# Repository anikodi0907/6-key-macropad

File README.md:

# 6-key-macropad
A simple macropad with 6 switches. VIA compatible, uses arduino pro micro.

Follow the [build guide](https://github.com/anikodi0907/6-key-macropad/blob/main/Build%20guide.md) to build the pcb.

## Photos
Fully built

Design images

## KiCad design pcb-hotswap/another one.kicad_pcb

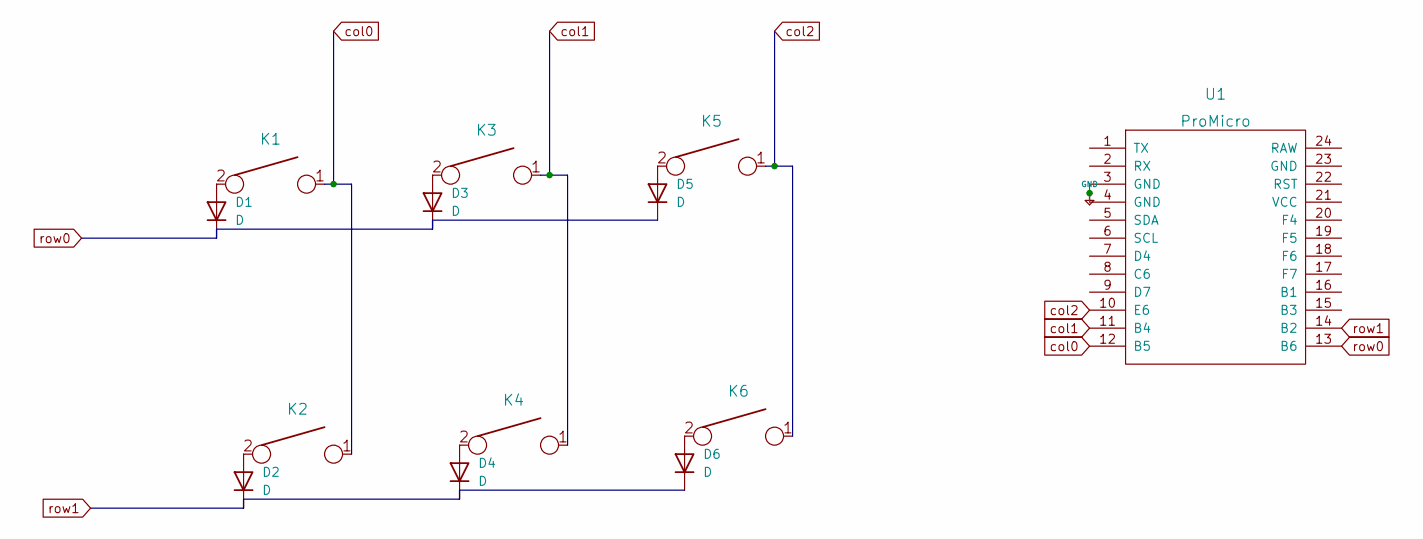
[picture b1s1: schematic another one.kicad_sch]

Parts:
D1, D2, D3, D4, D5, D6: D; D_SOD123_axial
K1, K2, K3, K4, K5: KEYSW; SW_Hotswap_Kailh_MX_1.00u
K6: KEYSW
U1: ProMicro

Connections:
+5V: U1.3 (GND), U1.4 (GND)
unnamed: D1.2 (A), K1.2
unnamed: D2.2 (A), K2.2
unnamed: D3.2 (A), K3.2
unnamed: D4.2 (A), K4.2
unnamed: D5.2 (A), K5.2
unnamed: D6.2 (A), K6.2
col0: K1.1, K2.1, U1.12 (B5)
col1: K3.1, K4.1, U1.11 (B4)
col2: K5.1, K6.1, U1.10 (E6)
row0: D1.1 (K), D3.1 (K), D5.1 (K), U1.13 (B6)
row1: D2.1 (K), D4.1 (K), D6.1 (K), U1.14 (B2)

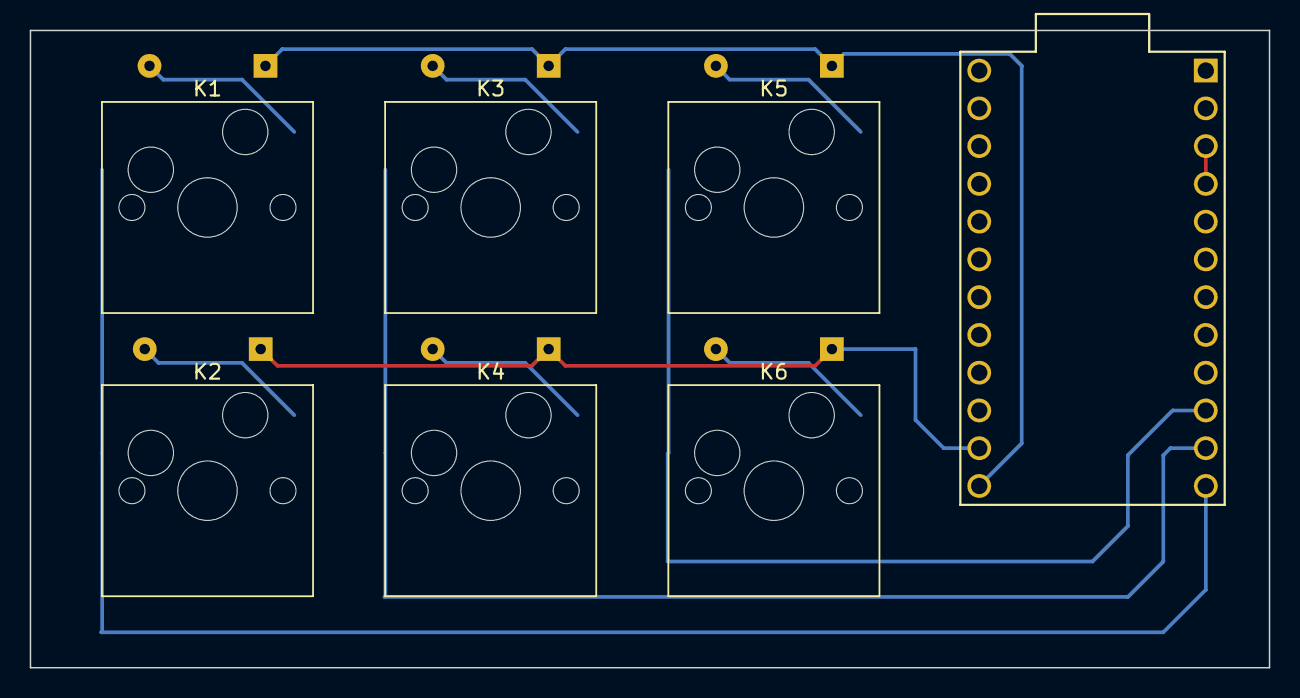
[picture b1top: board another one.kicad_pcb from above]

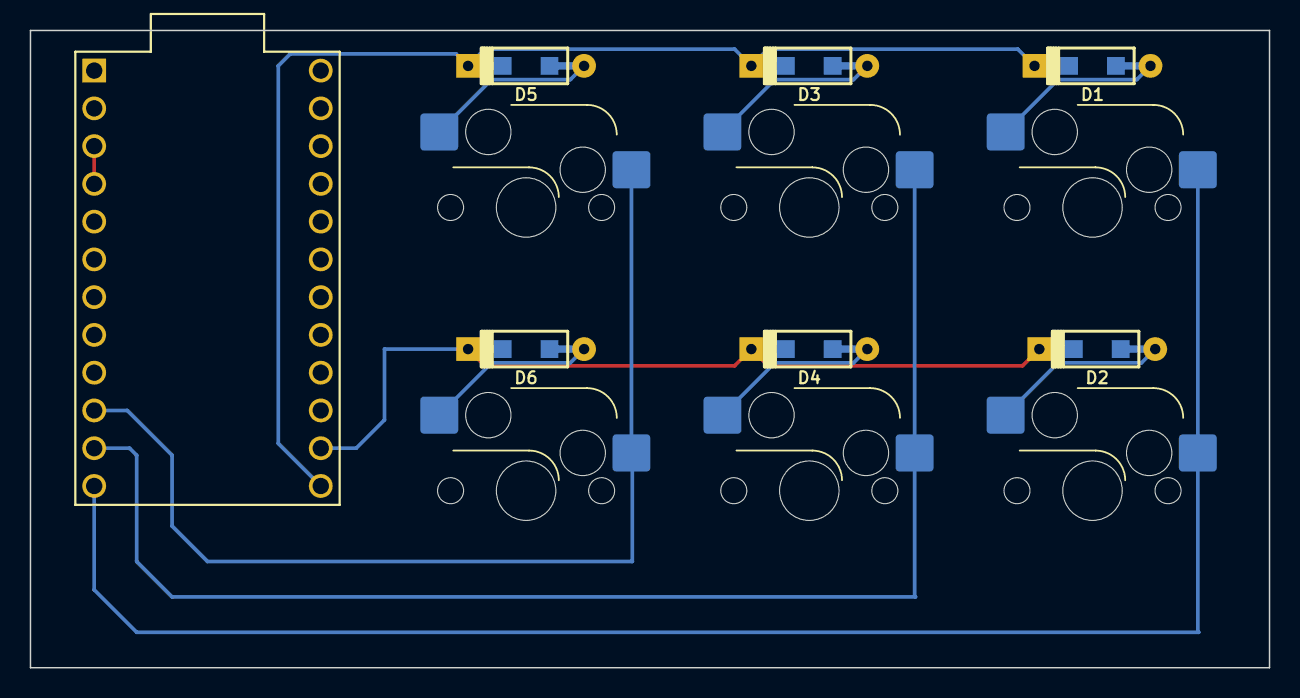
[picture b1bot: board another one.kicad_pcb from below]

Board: 2 copper layers, 83.3 x 42.9 mm, 13 parts (7 on the bottom side), 12 nets.

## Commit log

2022-08-06 Create pcb
2022-08-06 Create Build guide
